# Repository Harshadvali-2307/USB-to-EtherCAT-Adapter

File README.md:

# USB-to-EtherCAT-Adapter
STM32-based USB to EtherCAT adapter board using the LAN9252 EtherCAT controller.
Topics:
ethercat stm32 lan9252 usb embedded-systems pcb-design hardware industrial-automation electronics
Hardware design files and documentation for a USB-to-EtherCAT adapter board based on STM32 and LAN9252.

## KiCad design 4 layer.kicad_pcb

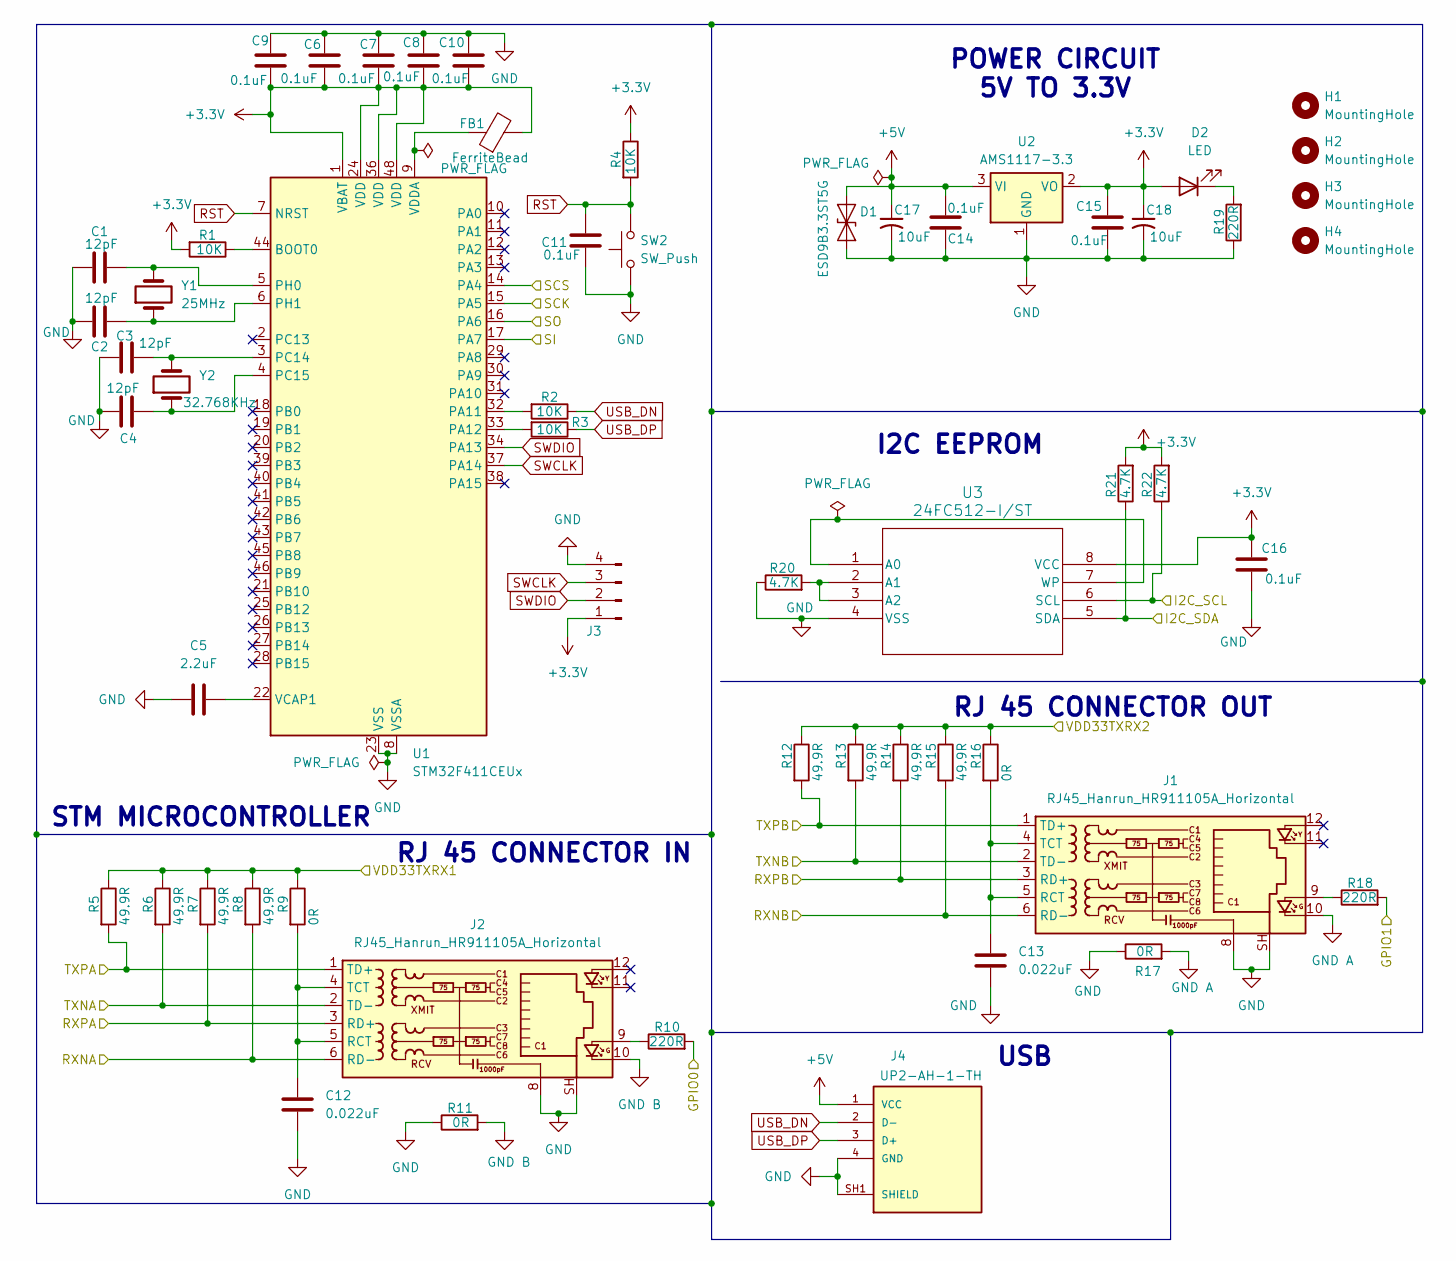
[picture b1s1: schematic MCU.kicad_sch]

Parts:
C1, C2, C3, C4: 12pF; C_0805_2012Metric
C5: 2.2uF; C_0805_2012Metric
C6, C7, C8, C9, C10, C11, C14, C15, C16: 0.1uF; C_0805_2012Metric
C12, C13: 0.022uF; C_0805_2012Metric
C17, C18: 10uF; C_1206_3216Metric
D1: ESD9B3.3ST5G; D_SOD-923
D2: LED; LED_0805_2012Metric
FB1: FerriteBead; C_0805_2012Metric
H1, H2, H3, H4: MountingHole; MountingHole_2.1mm
J1, J2: RJ45_Hanrun_HR911105A_Horizontal
J3: Conn_01x04_Pin; PinHeader_1x04_P2.54mm_Vertical
J4: UP2-AH-1-TH; usb cup type
R1, R2, R3, R4: 10K; R_0805_2012Metric
R5, R6, R7, R8, R12, R13, R14, R15: 49.9R; R_0805_2012Metric
R9, R11, R16, R17: 0R; R_0805_2012Metric
R10, R18, R19: 220R; R_0805_2012Metric
R20, R21, R22: 4.7K; R_0805_2012Metric
SW2: SW_Push; SW_Push_SPST_NO_Alps_SKRK
U1: STM32F411CEUx; QFN-48-1EP_7x7mm_P0.5mm_EP5.6x5.6mm
U2: AMS1117-3.3; SOT-223-3_TabPin2
U3: 24FC512-I/ST; 24FC512
Y1: 25MHz; Crystal_SMD_HC49-SD
Y2: 32.768KHz; Crystal_SMD_3215-2Pin_3.2x1.5mm

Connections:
+3.3V: C6.1, C7.1, C8.1, C9.1, C10.1, C15.2, C16.2, C18.1, D2.2 (A), FB1.2, J3.1, R1.2, R4.1, R21.2, R22.2, U1.1 (VBAT), U1.24 (VDD), U1.36 (VDD), U1.48 (VDD), U2.2 (VO), U3.8 (VCC); also elsewhere on the board
+5V: C14.1, C17.1, D1.1 (A1), J4.1 (VCC), U2.3 (VI)
/LAN925I/GPIO0: R10.2; also elsewhere on the board
/LAN925I/GPIO1: R18.2; also elsewhere on the board
/LAN925I/I2C_SCL: R21.1, U3.5 (SDA); also elsewhere on the board
/LAN925I/I2C_SDA: R22.1, U3.6 (SCL); also elsewhere on the board
/LAN925I/RXNA: J2.6 (RD-), R8.2; also elsewhere on the board
/LAN925I/RXNB: J1.6 (RD-), R15.2; also elsewhere on the board
/LAN925I/RXPA: J2.3 (RD+), R7.2; also elsewhere on the board
/LAN925I/RXPB: J1.3 (RD+), R14.2; also elsewhere on the board
/LAN925I/SCK: U1.15 (PA5); also elsewhere on the board
/LAN925I/SCS: U1.14 (PA4); also elsewhere on the board
/LAN925I/SI: U1.17 (PA7); also elsewhere on the board
/LAN925I/SO: U1.16 (PA6); also elsewhere on the board
/LAN925I/TXNA: J2.2 (TD-), R6.2; also elsewhere on the board
/LAN925I/TXNB: J1.2 (TD-), R13.2; also elsewhere on the board
/LAN925I/TXPA: J2.1 (TD+), R5.2; also elsewhere on the board
/LAN925I/TXPB: J1.1 (TD+), R12.2; also elsewhere on the board
GND: C1.1, C2.1, C3.1, C4.1, C5.1, C6.2, C7.2, C8.2, C9.2, C10.2, C11.1, C12.1, C13.1, C14.2, C15.1, C16.1, C17.2, C18.2, D1.2 (A2), J1.8, J1.SH, J2.8, J2.SH, J3.4, J4.4 (GND), J4.SH1 (SHIELD), J4.SH2 (SHIELD), R11.1, R17.1, R19.1, R20.1, SW2.1, U1.8 (VSSA), U1.23 (VSS), U1.35 (VSS), U1.47 (VSS), U1.49 (VSS), U2.1 (GND), U3.4 (VSS); also elsewhere on the board
GND A: J1.10, R17.2
GND B: J2.10, R11.2
unnamed: D2.1 (K), R19.2
unnamed: J1.9, R18.1
unnamed: C13.2, J1.4 (TCT), J1.5 (RCT), R16.2
unnamed: J2.9, R10.1
unnamed: C12.2, J2.4 (TCT), J2.5 (RCT), R9.2
unnamed: R1.1, U1.44 (BOOT0)
unnamed: R2.2, U1.32 (PA11)
unnamed: R3.2, U1.33 (PA12)
unnamed: C3.2, U1.3 (PC14), Y2.2
unnamed: C4.2, U1.4 (PC15), Y2.1
unnamed: C1.2, U1.5 (PH0), Y1.2
unnamed: C2.2, U1.6 (PH1), Y1.1
unnamed: C5.2, U1.22 (VCAP1)
unnamed: FB1.1, U1.9 (VDDA)
unnamed: U3.1 (A0), U3.7 (WP)
unnamed: R20.2, U3.2 (A1), U3.3 (A2)
RST: C11.2, R4.2, SW2.2, U1.7 (NRST)
SWCLK: J3.3, U1.37 (PA14)
SWDIO: J3.2, U1.34 (PA13)
USB_DN: J4.2 (D-), R2.1
USB_DP: J4.3 (D+), R3.1
VDD33TXRX1: R5.1, R6.1, R7.1, R8.1, R9.1; also elsewhere on the board
VDD33TXRX2: R12.1, R13.1, R14.1, R15.1, R16.1; also elsewhere on the board

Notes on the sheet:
RJ 45 CONNECTOR IN
RJ 45 CONNECTOR OUT
POWER CIRCUIT 5V TO 3.3V
STM MICROCONTROLLER
I2C EEPROM
USB

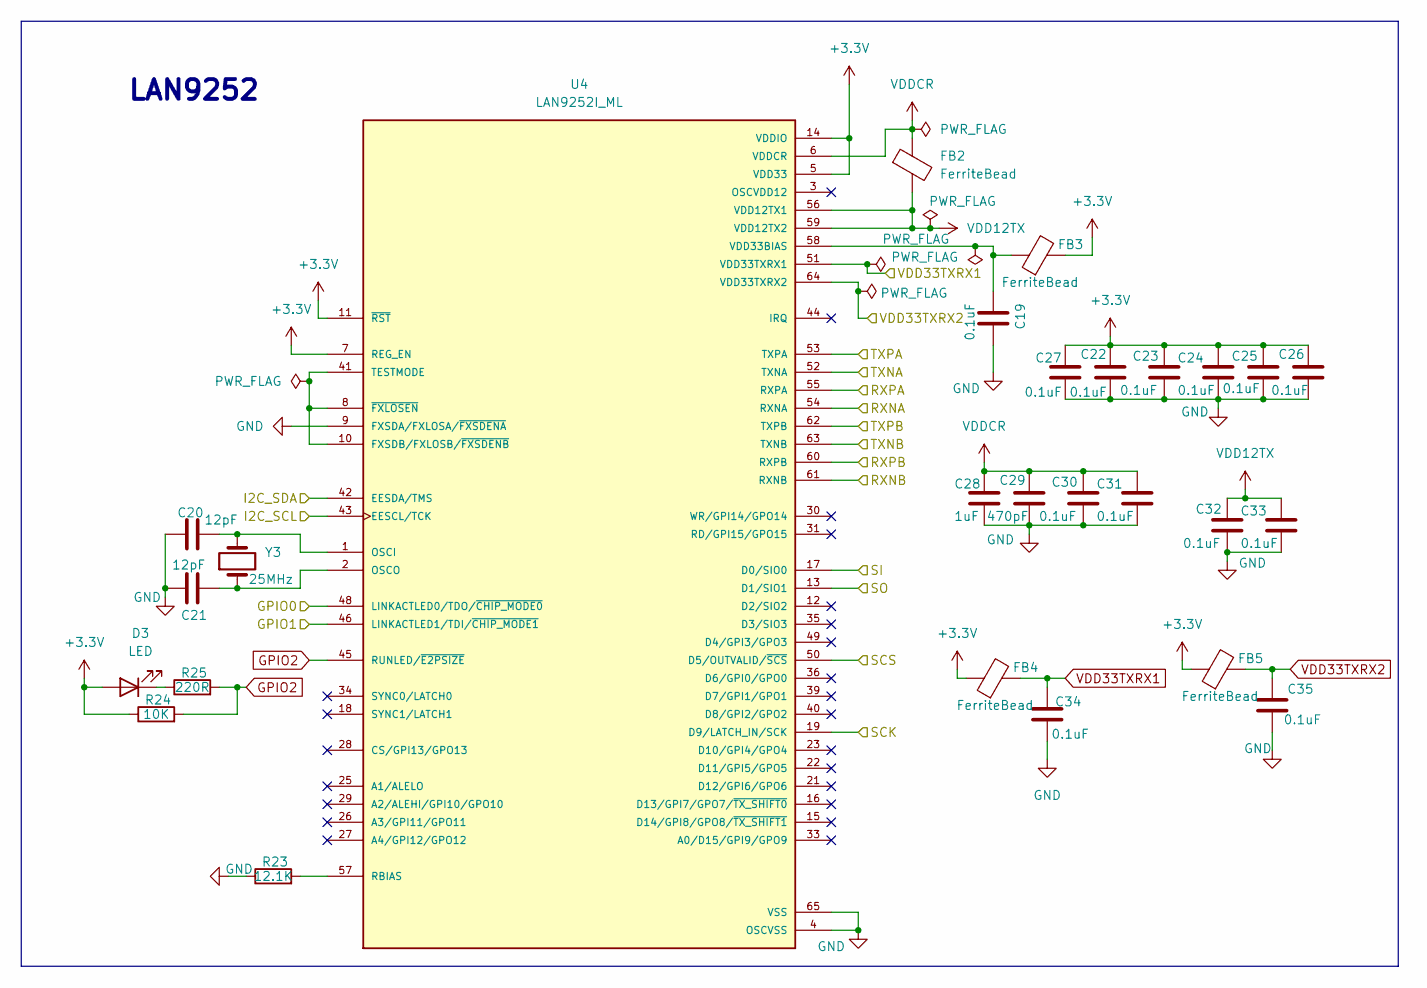
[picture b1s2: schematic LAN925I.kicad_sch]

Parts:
C19, C22, C23, C24, C25, C26, C27, C30, C31, C32, C33, C34, C35: 0.1uF; C_0805_2012Metric
C20, C21: 12pF; C_0805_2012Metric
C28: 1uF; C_0805_2012Metric
C29: 470pF; C_0805_2012Metric
D3: LED; LED_0805_2012Metric
FB2, FB3, FB4, FB5: FerriteBead; C_0805_2012Metric
R23: 12.1K; R_0805_2012Metric
R24: 10K; R_0805_2012Metric
R25: 220R; R_0805_2012Metric
U4: LAN9252I_ML; LAM ML IC
Y3: 25MHz; Crystal_SMD_HC49-SD

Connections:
+3.3V: C22.2, C23.2, C24.2, C25.2, C26.2, C27.2, D3.2 (A), FB3.2, FB4.1, FB5.1, R24.1, U4.5 (VDD33), U4.7 (REG_EN), U4.11 (~RST), U4.14 (VDDIO), U4.20 (VDDIO), U4.32 (VDDIO), U4.37 (VDDIO), U4.47 (VDDIO); also elsewhere on the board
/LAN925I/GPIO0: U4.48 (LINKACTLED0/TDO/~CHIP_MODE0); also elsewhere on the board
/LAN925I/GPIO1: U4.46 (LINKACTLED1/TDI/~CHIP_MODE1); also elsewhere on the board
/LAN925I/I2C_SCL: U4.43 (EESCL/TCK); also elsewhere on the board
/LAN925I/I2C_SDA: U4.42 (EESDA/TMS); also elsewhere on the board
/LAN925I/RXNA: U4.54 (RXNA); also elsewhere on the board
/LAN925I/RXNB: U4.61 (RXNB); also elsewhere on the board
/LAN925I/RXPA: U4.55 (RXPA); also elsewhere on the board
/LAN925I/RXPB: U4.60 (RXPB); also elsewhere on the board
/LAN925I/SCK: U4.19 (D9/LATCH_IN/SCK); also elsewhere on the board
/LAN925I/SCS: U4.50 (D5/OUTVALID/~SCS); also elsewhere on the board
/LAN925I/SI: U4.17 (D0/SIO0); also elsewhere on the board
/LAN925I/SO: U4.13 (D1/SIO1); also elsewhere on the board
/LAN925I/TXNA: U4.52 (TXNA); also elsewhere on the board
/LAN925I/TXNB: U4.63 (TXNB); also elsewhere on the board
/LAN925I/TXPA: U4.53 (TXPA); also elsewhere on the board
/LAN925I/TXPB: U4.62 (TXPB); also elsewhere on the board
GND: C19.1, C20.1, C21.1, C22.1, C23.1, C24.1, C25.1, C26.1, C27.1, C28.1, C29.1, C30.1, C31.1, C32.1, C33.1, C34.1, C35.1, R23.1, U4.4 (OSCVSS), U4.9 (FXSDA/FXLOSA/~FXSDENA), U4.65 (VSS), U4.66, U4.67, U4.68, U4.69, U4.70, U4.71, U4.72, U4.73, U4.74, U4.75, U4.76, U4.77, U4.78, U4.79, U4.80, U4.81, U4.82, U4.83, U4.84, U4.85, U4.86, U4.87, U4.88, U4.89, U4.90, U4.91, U4.92, U4.93, U4.94, U4.95, U4.96, U4.97, U4.98, U4.99, U4.100, U4.101; also elsewhere on the board
GPIO2: R24.2, R25.2, U4.45 (RUNLED/~E2PSIZE)
unnamed: D3.1 (K), R25.1
unnamed: U4.8 (~FXLOSEN), U4.10 (FXSDB/FXLOSB/~FXSDENB), U4.41 (TESTMODE)
unnamed: C20.2, U4.1 (OSCI), Y3.2
unnamed: C21.2, U4.2 (OSCO), Y3.1
unnamed: R23.2, U4.57 (RBIAS)
unnamed: C19.2, FB3.1, U4.58 (VDD33BIAS)
VDD12TX: C32.2, C33.2, FB2.2, U4.56 (VDD12TX1), U4.59 (VDD12TX2)
VDD33TXRX1: C34.2, FB4.2, U4.51 (VDD33TXRX1); also elsewhere on the board
VDD33TXRX2: C35.2, FB5.2, U4.64 (VDD33TXRX2); also elsewhere on the board
VDDCR: C28.2, C29.2, C30.2, C31.2, FB2.1, U4.6 (VDDCR), U4.24 (VDDCR), U4.38 (VDDCR)

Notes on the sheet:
LAN9252

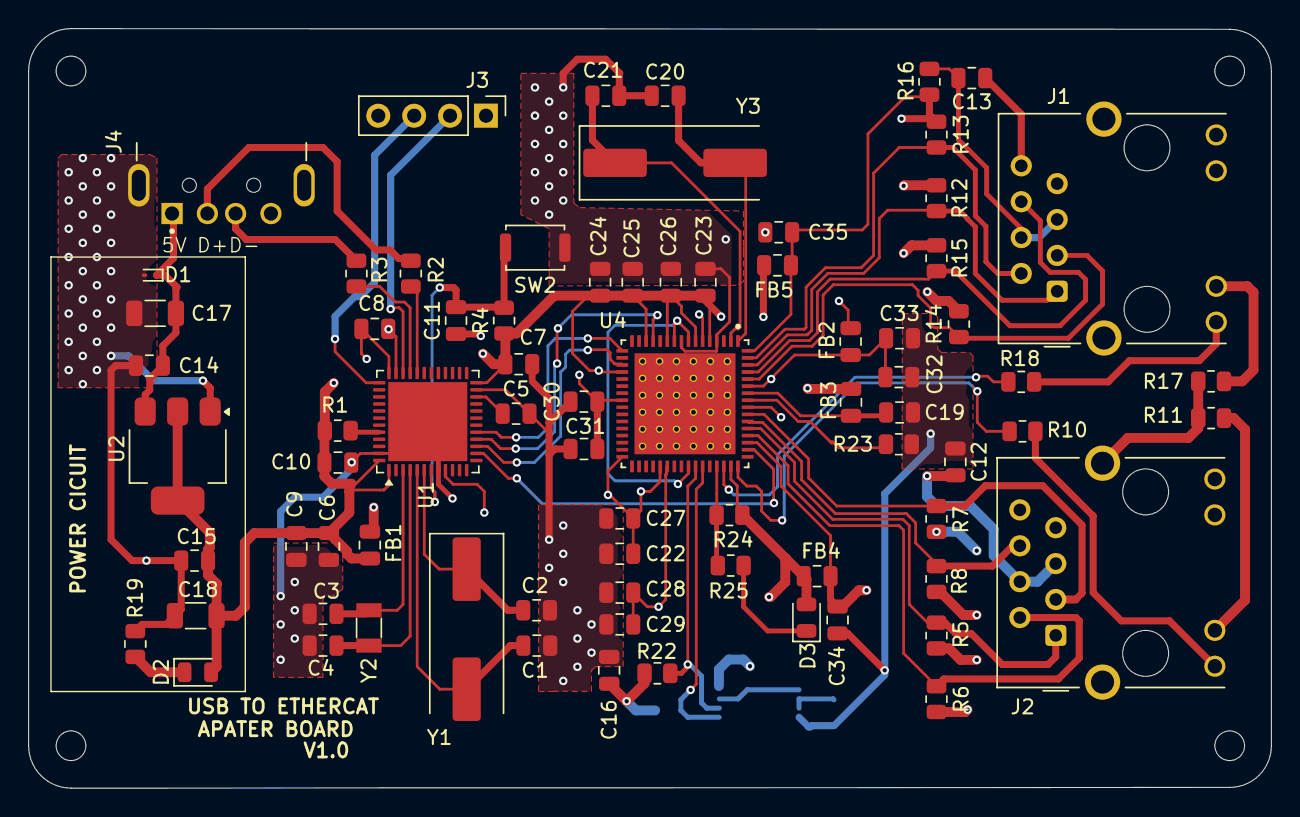
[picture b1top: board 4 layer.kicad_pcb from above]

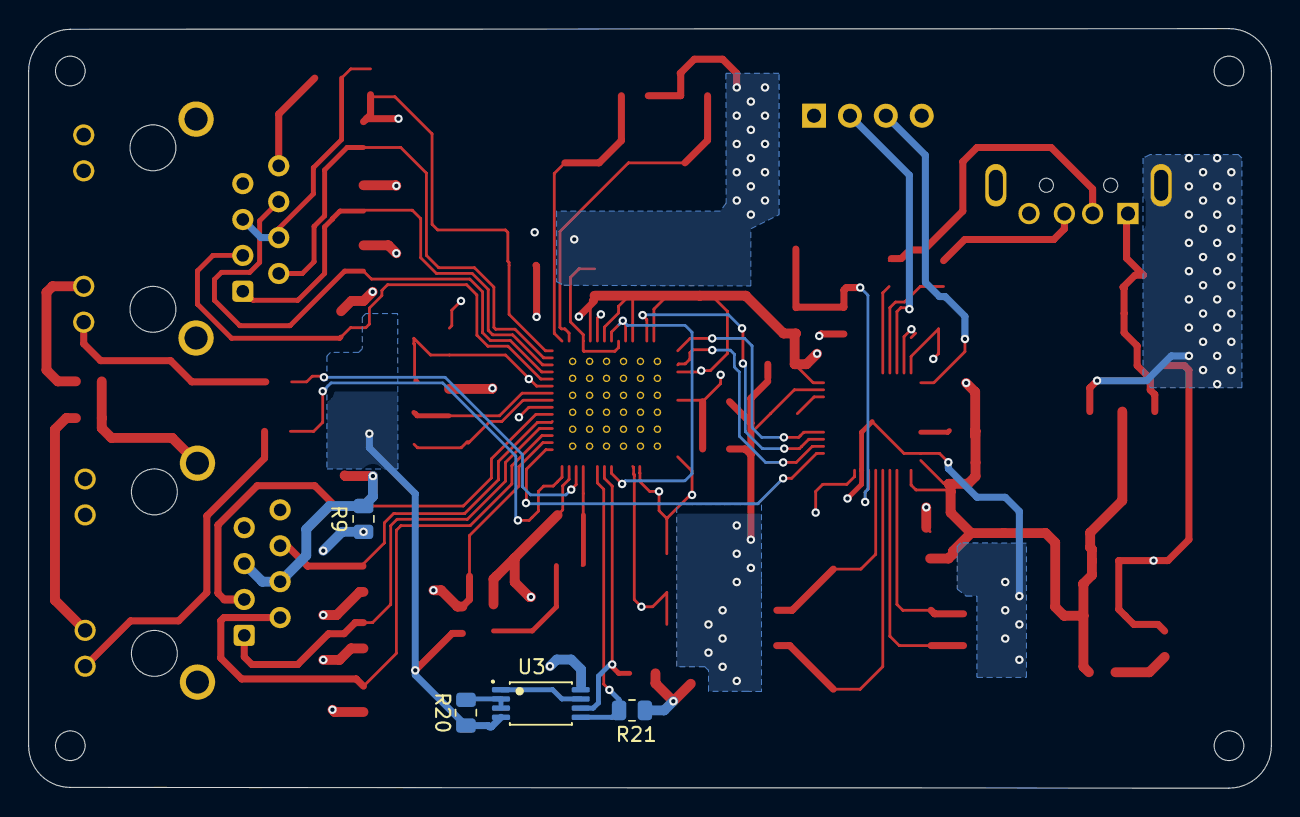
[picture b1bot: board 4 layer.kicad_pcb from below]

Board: 4 copper layers, 87.9 x 53.8 mm, 84 parts (4 on the bottom side), 53 nets.

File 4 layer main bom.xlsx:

Reference | Value | Datasheet | Footprint | DNP | Exclude from BOM | Exclude from Board | Qty | manufacture number | MANUFACTURER
C1,C2,C3,C4,C20,C21 | 12pF | ~https://datasheets.kyocera-avx.com/600S.pdf | Capacitor_SMD:C_0805_2012Metric |  |  |  | 6 | 600S120JT250XT4K | KYOCERA AVX
C5 | 2.2uF | https://www.mouser.in/datasheet/3/72/1/T491C335K036AT.pdf | Capacitor_SMD:C_0805_2012Metric |  |  |  | 1 | 0805X225M100CT | Walsin
C6,C7,C8,C9,C10,C11,C14,C15,C16,C19,C22,C23,C24,C25,C26,C27,C30,C31,C32,C33,C34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 | 0.1uF | ~https://mm.digikey.com/Volume0/opasdata/d220001/medias/docus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 | Capacitor_SMD:C_0805_2012Metric |  |  |  | 22 | 0805B104K500BD | Aillen
C12,C13 | 0.022uF | https://mm.digikey.com/Volume0/opasdata/d220001/medias/docus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 | Capacitor_SMD:C_0805_2012Metric |  |  |  | 2 | 0805B223K101BD | Aillen
C17,C18 | 10uF | https://www.mouser.in/datasheet/3/72/1/KEM_T2009_T495.pdf,~ | Capacitor_SMD:C_1206_3216Metric |  |  |  | 2 | T495C106M025ATE300 | KEMET
C28 | 1uF | https://mm.digikey.com/Volume0/opasdata/d220001/medias/docus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 | Capacitor_SMD:C_0805_2012Metric |  |  |  | 1 | 0805B105K100CC | Aillen
C29 | 470pF | ~https://mm.digikey.com/Volume0/opasdata/d220001/medias/docus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 | Capacitor_SMD:C_0805_2012Metric |  |  |  | 1 | 0805B471K101BD | Aillen
D1 | ESD9B3.3ST5G | https://www.onsemi.com/pub/Collateral/ESD9B-D.PDF | Diode_SMD:D_SOD-923 |  |  |  | 1 | ESD9B3.3ST5G | onsemi
D2,D3 | LED | ~https://www.we-online.com/components/products/datasheet/1500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 | LED_SMD:LED_0805_2012Metric |  |  |  | 2 | 150080RS75000 | WÃƒÂ¼rth Elektronik
FB1,FB2,FB3,FB4,FB5 | FerriteBead | https://www.laird.com/sites/default/files/mi0805k400r-10-dat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 | Capacitor_SMD:C_0805_2012Metric |  |  |  | 5 | MI0805K400R-10 | Laird-Signal Integrity Products
H1,H2,H3,H4 | MountingHole | ~ | MountingHole:MountingHole_2.1mm |  | Excluded from BOM |  | 4
J1,J2 | RJ45_Hanrun_HR911105A_Horizontal | https://datasheet.lcsc.com/lcsc/1811141815_HANRUN-Zhongshan-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 | Connector_RJ:RJ45_Hanrun_HR911105A_Horizontal |  |  |  | 2 | HR911105A | Hanrun Electronics
J3 | Conn_01x04_Pin | ~https://content.harwin.com/m/0351a4d2df127c05/original/DRG-0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 | Connector_PinHeader_2.54mm:PinHeader_1x04_P2.54mm_Vertical |  |  |  | 1 | D01-9922046 | Harwin Inc.
J4 | UP2-AH-1-TH | https://www.sameskydevices.com/product/resource/up2-ah-th.pdf | usb type c:usb cup type |  |  |  | 1 | UP2-AH-1-TH | Same Sky (Formerly CUI Devices)
R1,R2,R3,R4,R24 | 10K | https://yageogroup.com/content/datasheet/asset/file/PYU-RC_G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 | Resistor_SMD:R_0805_2012Metric |  |  |  | 5 | RC0805JR-0710KL | YAGEO
R5,R6,R7,R8,R12,R13,R14,R15 | 49.9R | https://www.vishay.com/docs/20043/crcwhpe3.pdf | Resistor_SMD:R_0805_2012Metric |  |  |  | 8 | CRCW080549R9FKEAHP | Vishay Dale
R9,R11,R16,R17 | 0R | ~https://yageogroup.com/content/datasheet/asset/file/PYU-RC_G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 | Resistor_SMD:R_0805_2012Metric |  |  |  | 4 | RC0805JR-070RL | YAGEO
R10,R18,R19,R25 | 220R | ~https://www.te.com/commerce/DocumentDelivery/DDEController?A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 | Resistor_SMD:R_0805_2012Metric |  |  |  | 4 | CRGCQ0805F220R | TE Connectivity Passive Product
R20,R21,R22 | 4.7K | https://industrial.panasonic.com/cdbs/www-data/pdf/RDO0000/A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 | Resistor_SMD:R_0805_2012Metric |  |  |  | 3 | ERJ-P06J472V | Panasonic Electronic Components
R23 | 12.1K | https://www.vishay.com/docs/28773/crcwce3.pdf | Resistor_SMD:R_0805_2012Metric |  |  |  | 1 | CRCW080512K1FKEAC | Vishay Dale
SW2 | SW_Push | ~~https://www.te.com/commerce/DocumentDelivery/DDEController?A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 | Button_Switch_SMD:SW_Push_SPST_NO_Alps_SKRK |  |  |  | 1 | 1571563-6 | TE Connectivity / P&B
U1 | STM32F411CEUx | https://www.st.com/resource/en/datasheet/stm32f411ce.pdf | Package_DFN_QFN:QFN-48-1EP_7x7mm_P0.5mm_EP5.6x5.6mm |  |  |  | 1 | STM32F411CEU6TR | STMicroelectronics
U2 | AMS1117-3.3 | http://www.advanced-monolithic.com/pdf/ds1117.pdf | Package_TO_SOT_SMD:SOT-223-3_TabPin2 |  |  |  | 1 | AMS1117-3.3 | EVVO
U3 | 24FC512-I/ST | https://ww1.microchip.com/downloads/en/DeviceDoc/24AA512-24L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 | usb type c:24FC512 |  |  |  | 1 | 24FC512-I/ST | Microchip Technology
U4 | LAN9252I_ML | https://ww1.microchip.com/downloads/aemDocuments/documents/O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 | usb type c:LAM ML IC |  |  |  | 1 | LAN9252I/ML | Microchip Technology
Y1,Y3 | 25MHz | https://mm.digikey.com/Volume0/opasdata/d220001/medias/docus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 | Crystal:Crystal_SMD_HC49-SD |  |  |  | 2 | SD2025M00012T1521006 | Hefei Jingweite Electronics Co., Ltd.
Y2 | 32.768KHz | https://www.yic.com.tw/wp-content/uploads/2025/04/YIC-3215A-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 | Crystal:Crystal_SMD_3215-2Pin_3.2x1.5mm |  |  |  | 1 | 32.768K12.5PI/3215A | YIC
